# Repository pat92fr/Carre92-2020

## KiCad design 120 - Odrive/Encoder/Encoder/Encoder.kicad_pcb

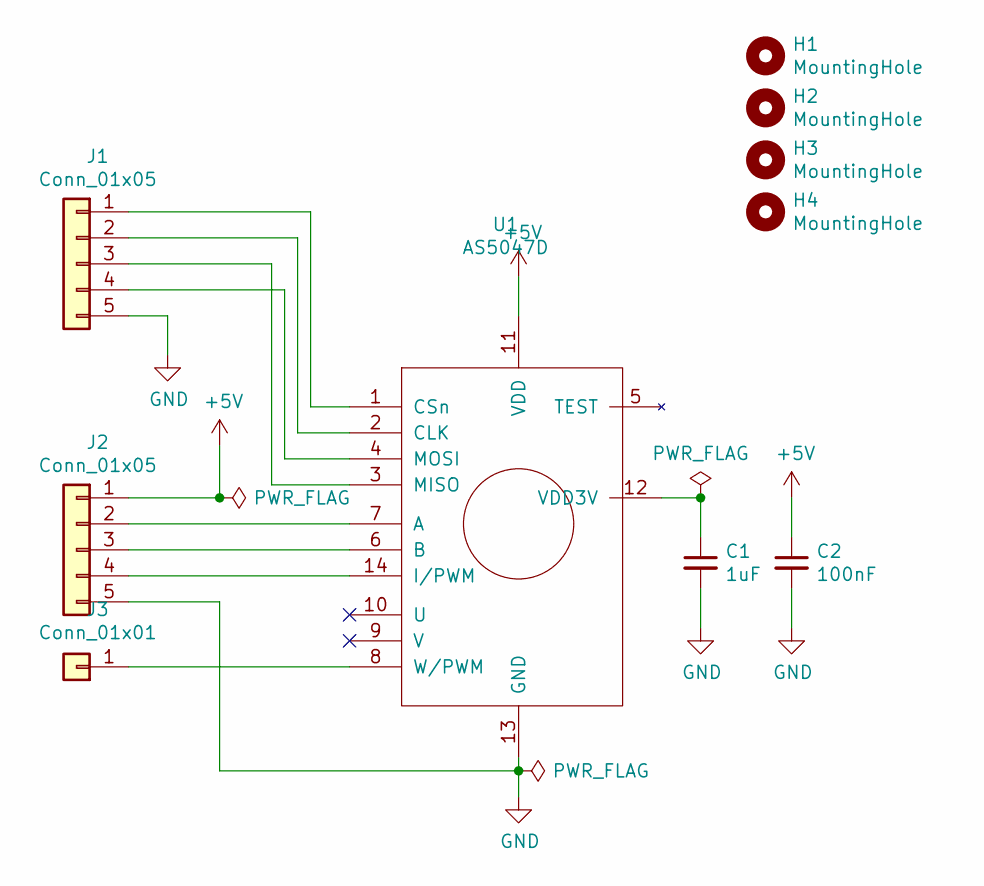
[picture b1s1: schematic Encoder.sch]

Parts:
C1: 1uF; C_0603_HandSoldering
C2: 100nF; C_0603_HandSoldering
H1, H2, H3, H4: MountingHole; MountingHole_4.3mm_M4
J1, J2: Conn_01x05; Pin_Header_Straight_1x05_Pitch2.54mm
J3: Conn_01x01; Pin_Header_Straight_1x01_Pitch2.54mm
U1: AS5047D; TSSOP-14-1EP_4.4x5mm_Pitch0.65mm

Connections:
+5V: C2.1, J2.1, U1.11 (VDD)
GND: C1.2, C2.2, J1.5, J2.5, U1.13 (GND)
unnamed: C1.1, U1.12 (VDD3V)
unnamed: J1.1, U1.1 (CSn)
unnamed: J1.2, U1.2 (CLK)
unnamed: J1.3, U1.3 (MISO)
unnamed: J1.4, U1.4 (MOSI)
unnamed: J2.2, U1.7 (A)
unnamed: J2.3, U1.6 (B)
unnamed: J2.4, U1.14 (I/PWM)
unnamed: J3.1, U1.8 (W/PWM)

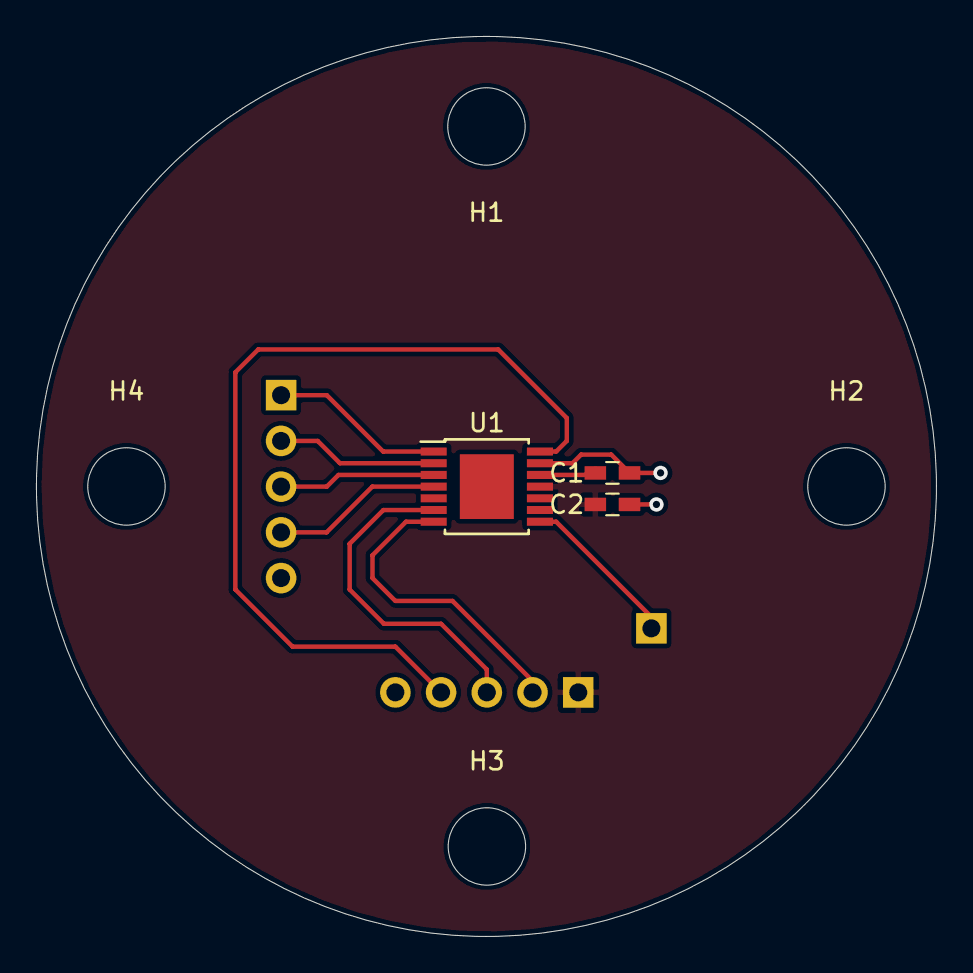
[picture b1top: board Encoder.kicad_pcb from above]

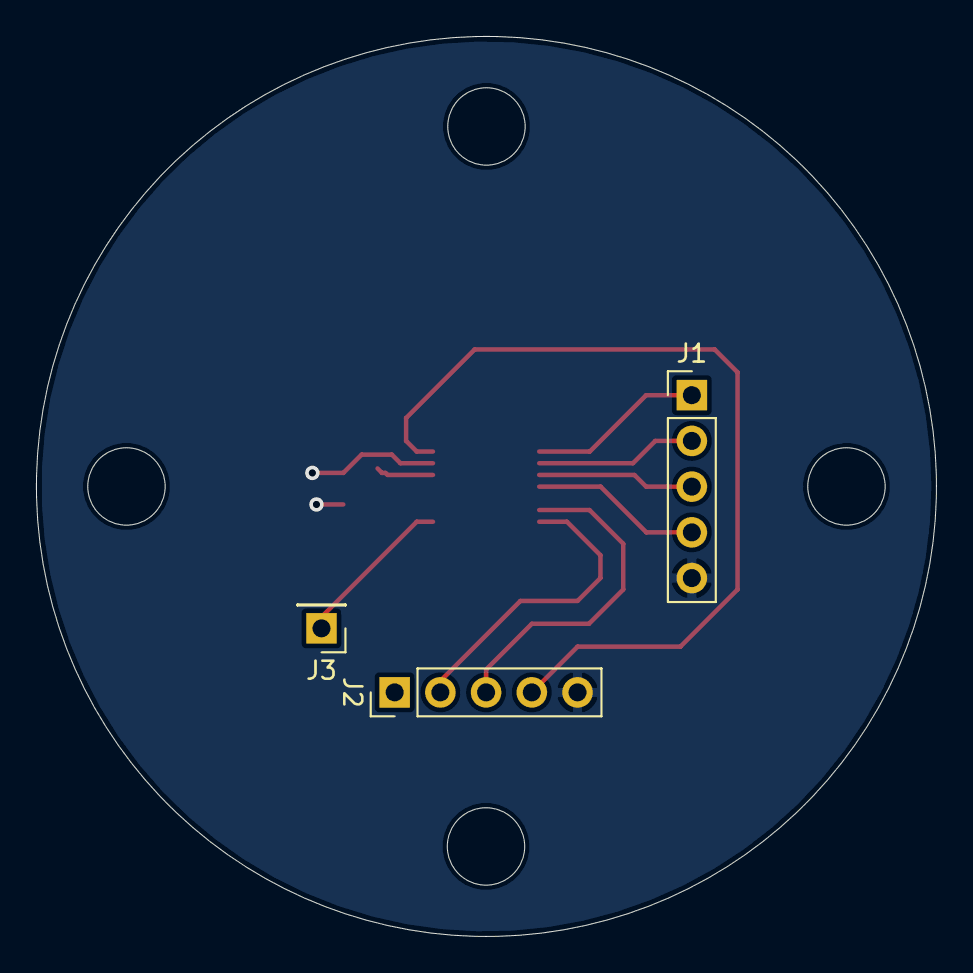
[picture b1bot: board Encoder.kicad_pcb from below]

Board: 2 copper layers, 50.0 x 50.0 mm, 10 parts (3 on the bottom side), 11 nets.

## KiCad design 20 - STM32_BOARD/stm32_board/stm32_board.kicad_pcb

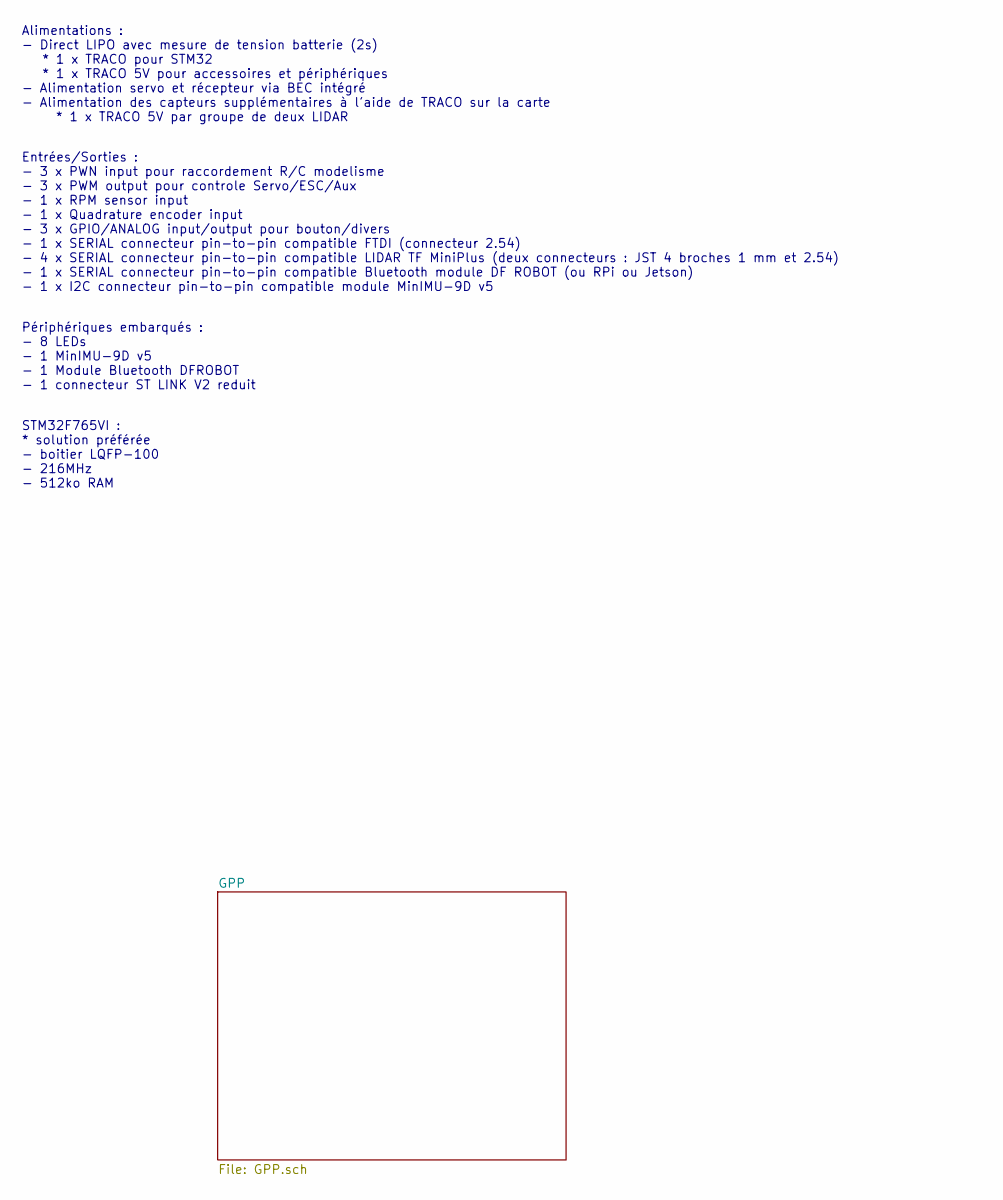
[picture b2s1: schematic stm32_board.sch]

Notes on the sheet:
Alimentations : - Direct LIPO avec mesure de tension batterie (2s) * 1 x TRACO pour STM32 * 1 x TRACO 5V pour accessoires et périphériques - Alimentation servo et récepteur via BEC intégré - Alimentation des capteurs supplémentaires à l'aide de TRACO sur la carte * 1 x TRACO 5V par groupe de deux L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
Entrées/Sorties : - 3 x PWN input pour raccordement R/C modelisme - 3 x PWM output pour controle Servo/ESC/Aux - 1 x RPM sensor input - 1 x Quadrature encoder input - 3 x GPIO/ANALOG input/output pour bouton/divers - 1 x SERIAL connecteur pin-to-pin compatible FTDI (connecteur 2.54) - 4 x SERIAL co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
Périphériques embarqués : - 8 LEDs - 1 MinIMU-9D v5 - 1 Module Bluetooth DFROBOT - 1 connecteur ST LINK V2 reduit
STM32F765VI : * solution préférée - boitier LQFP-100 - 216MHz - 512ko RAM

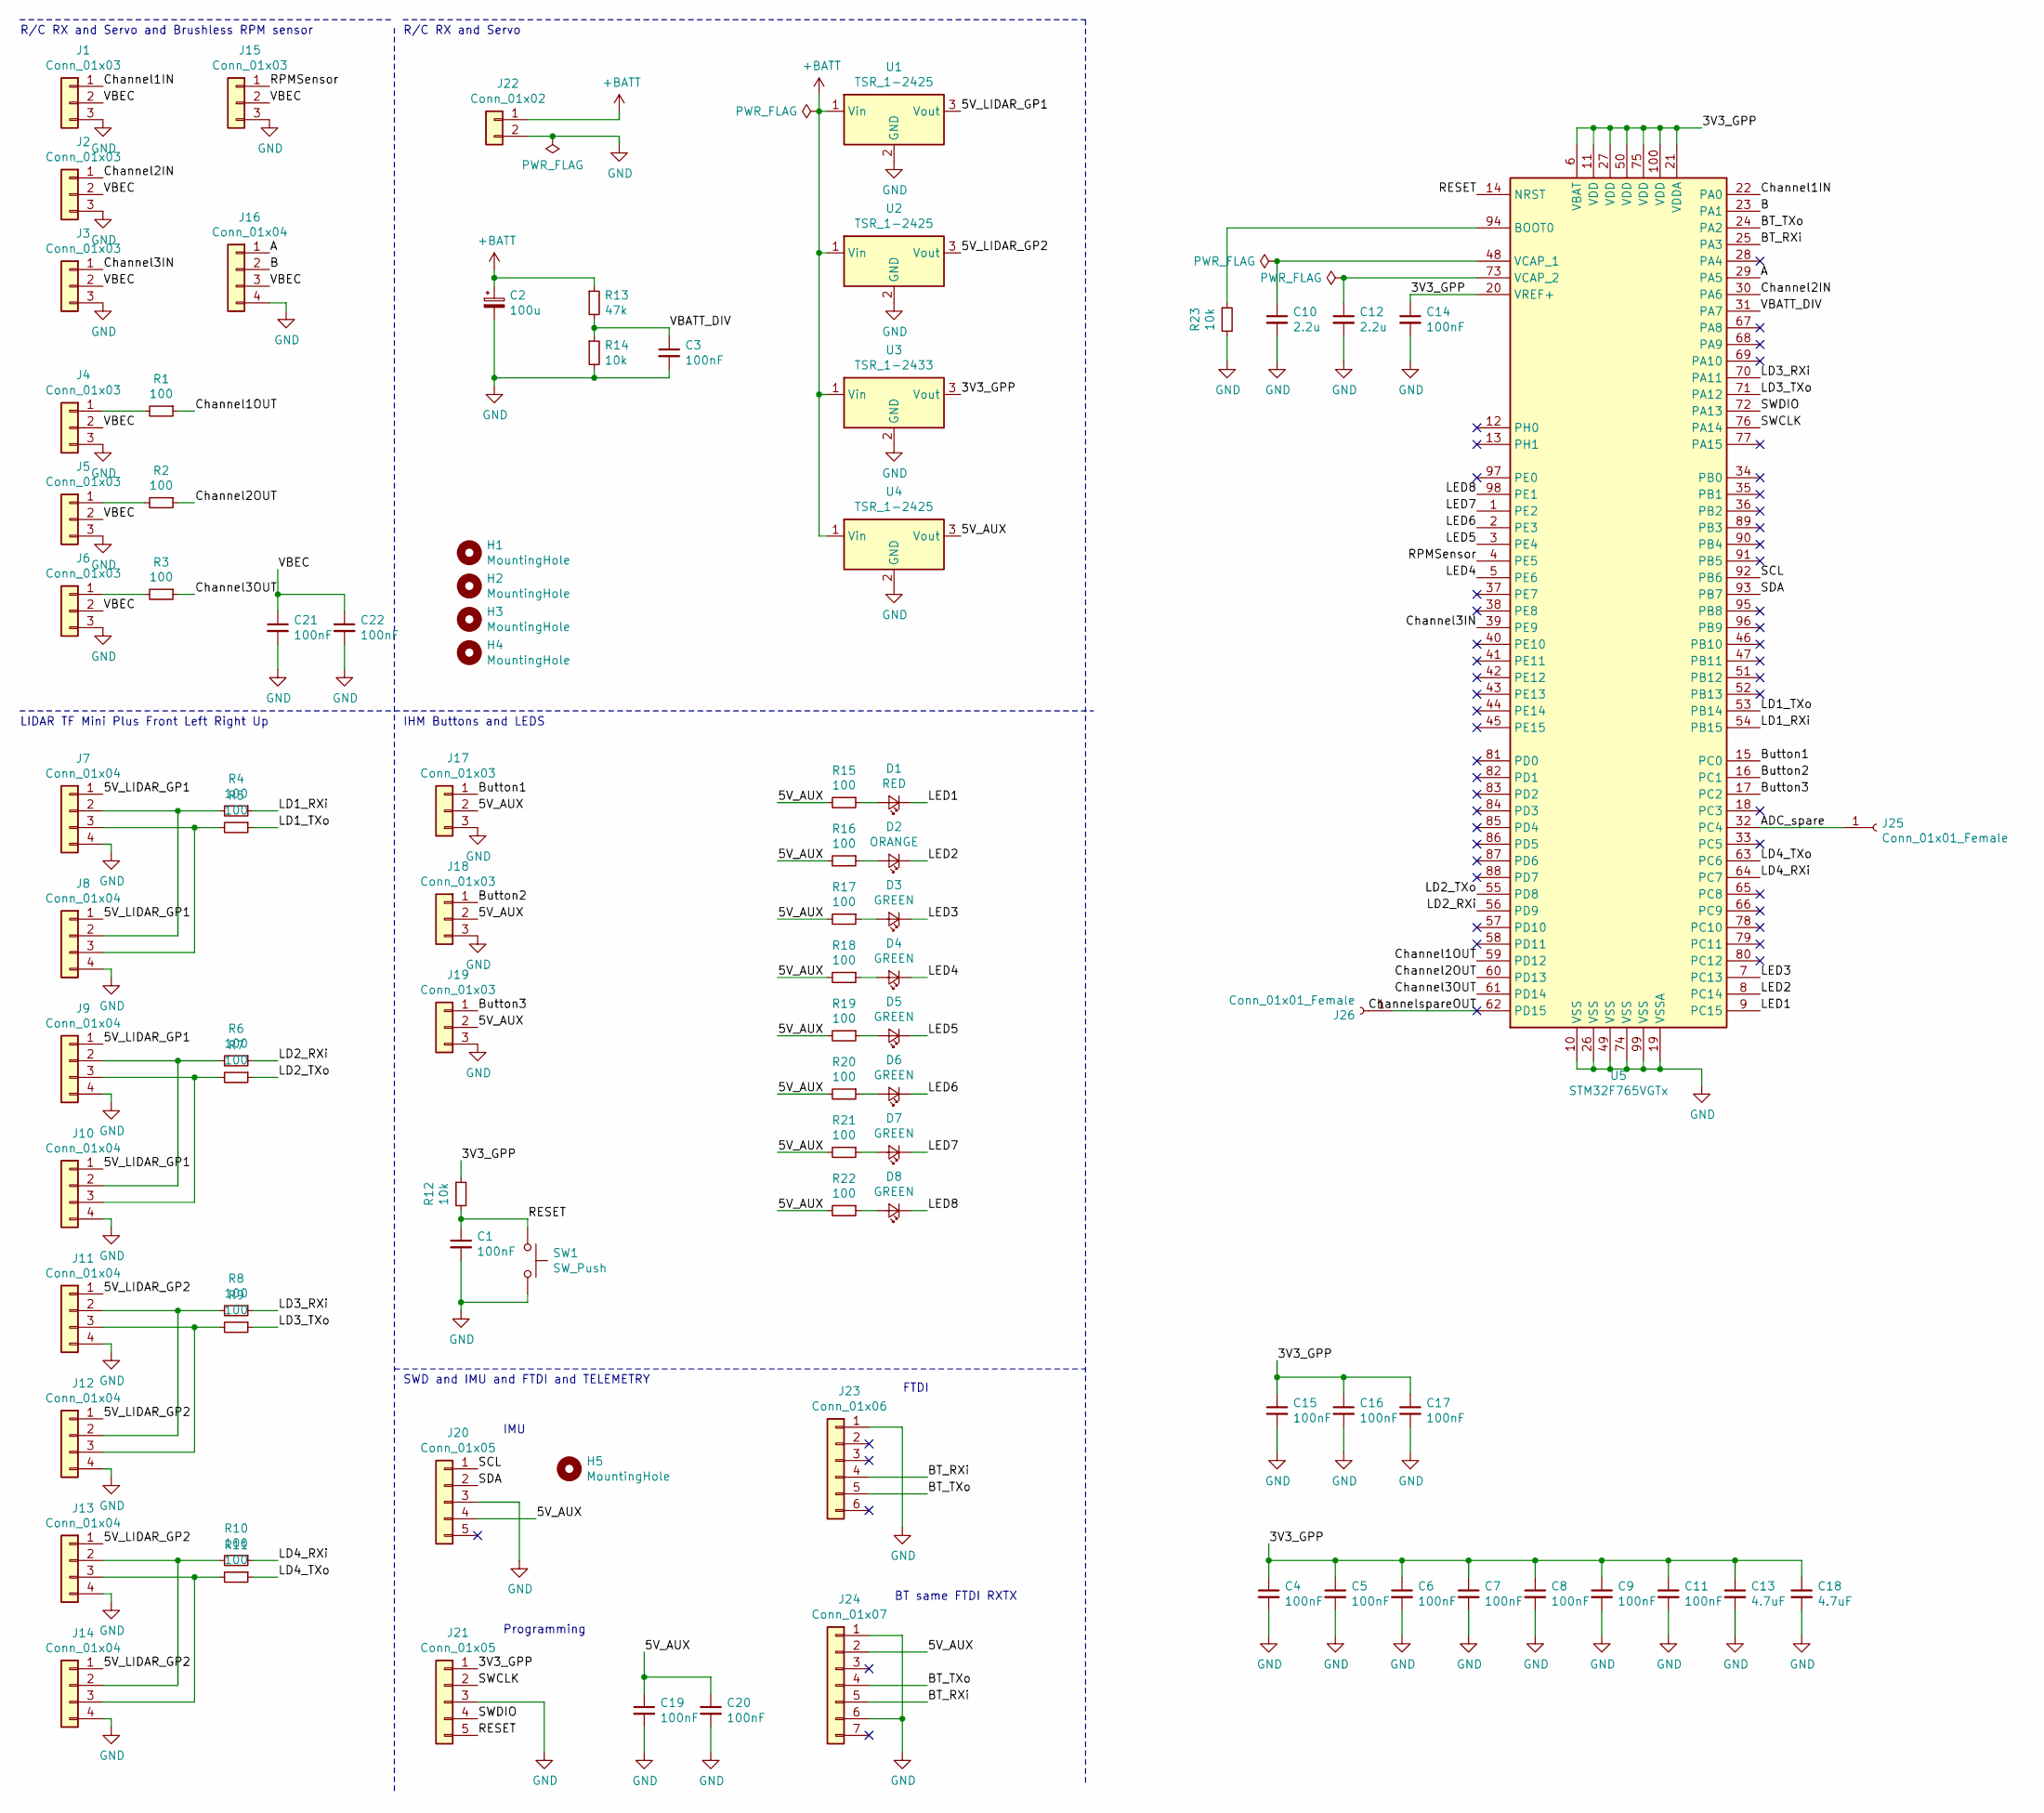
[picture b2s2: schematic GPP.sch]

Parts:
C1, C3, C4, C5, C6, C7, C8, C9, C11: 100nF; C_0603_1608Metric_Pad1.05x0.95mm_HandSolder
C2: 100u; CP_Elec_8x6.9
C10, C12: 2.2u; C_0603_1608Metric_Pad1.05x0.95mm_HandSolder
C13: 4.7uF; C_0603_1608Metric_Pad1.05x0.95mm_HandSolder
C14, C15, C16, C17, C19, C20, C21, C22: 100nF; C_0603_HandSoldering
C18: 4.7uF; C_0603_HandSoldering
D1: RED; LED_0805_2012Metric_Pad1.15x1.40mm_HandSolder
D2: ORANGE; LED_0805_2012Metric_Pad1.15x1.40mm_HandSolder
D3, D4, D5, D6, D7, D8: GREEN; LED_0805_2012Metric_Pad1.15x1.40mm_HandSolder
H1, H2, H3, H4, H5: MountingHole; MountingHole_3.2mm_M3
J1, J2, J3, J4, J5, J6, J15, J17, J18, J19: Conn_01x03; PinHeader_1x03_P2.54mm_Vertical
J7, J9, J11, J13: Conn_01x04; JST_SH_BM04B-SRSS-TB_1x04-1MP_P1.00mm_Vertical
J8, J10, J12, J14, J16: Conn_01x04; PinHeader_1x04_P2.54mm_Vertical
J20, J21: Conn_01x05; PinHeader_1x05_P2.54mm_Vertical
J22: Conn_01x02; PinHeader_1x02_P2.54mm_Vertical
J23: Conn_01x06; PinHeader_1x06_P2.54mm_Vertical
J24: Conn_01x07; PinHeader_1x07_P2.54mm_Vertical
J25, J26: Conn_01x01_Female; Pin_Header_Straight_1x01_Pitch2.54mm
R1, R2, R3, R4, R5, R6, R7, R8, R9, R10, R11, R15, R16, R17, R18, R19, R20, R21, R22: 100; R_0603_1608Metric_Pad1.05x0.95mm_HandSolder
R12, R14, R23: 10k; R_0603_1608Metric_Pad1.05x0.95mm_HandSolder
R13: 47k; R_0603_1608Metric_Pad1.05x0.95mm_HandSolder
SW1: SW_Push; SW_PUSH_6mm
U1, U2, U4: TSR_1-2425; Converter_DCDC_TRACO_TSR-1_THT
U3: TSR_1-2433; Converter_DCDC_TRACO_TSR-1_THT
U5: STM32F765VGTx; LQFP-100_14x14mm_P0.5mm

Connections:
+BATT: C2.1, J22.1, R13.1, U1.1 (Vin), U2.1 (Vin), U3.1 (Vin), U4.1 (Vin)
/GPP/3V3_GPP: C4.1, C5.1, C6.1, C7.1, C8.1, C9.1, C11.1, C13.1, C14.1, C15.1, C16.1, C17.1, C18.1, J21.1, R12.1, U3.3 (Vout), U5.6 (VBAT), U5.11 (VDD), U5.20 (VREF+), U5.21 (VDDA), U5.27 (VDD), U5.50 (VDD), U5.75 (VDD), U5.100 (VDD)
/GPP/5V_AUX: C19.1, C20.1, J17.2, J18.2, J19.2, J20.4, J24.2, R15.2, R16.2, R17.2, R18.2, R19.2, R20.2, R21.2, R22.2, U4.3 (Vout)
/GPP/5V_LIDAR_GP1: J7.1, J8.1, J9.1, J10.1, U1.3 (Vout)
/GPP/5V_LIDAR_GP2: J11.1, J12.1, J13.1, J14.1, U2.3 (Vout)
/GPP/A: J16.1, U5.29 (PA5)
/GPP/ADC_spare: J25.1, U5.32 (PC4)
/GPP/B: J16.2, U5.23 (PA1)
/GPP/BT_RXi: J23.4, J24.5, U5.25 (PA3)
/GPP/BT_TXo: J23.5, J24.4, U5.24 (PA2)
/GPP/Button1: J17.1, U5.15 (PC0)
/GPP/Button2: J18.1, U5.16 (PC1)
/GPP/Button3: J19.1, U5.17 (PC2)
/GPP/Channel1IN: J1.1, U5.22 (PA0)
/GPP/Channel1OUT: R1.1, U5.59 (PD12)
/GPP/Channel2IN: J2.1, U5.30 (PA6)
/GPP/Channel2OUT: R2.1, U5.60 (PD13)
/GPP/Channel3IN: J3.1, U5.39 (PE9)
/GPP/Channel3OUT: R3.1, U5.61 (PD14)
/GPP/ChannelspareOUT: J26.1, U5.62 (PD15)
/GPP/LD1_RXi: R4.1, U5.54 (PB15)
/GPP/LD1_TXo: R5.1, U5.53 (PB14)
/GPP/LD2_RXi: R6.1, U5.56 (PD9)
/GPP/LD2_TXo: R7.1, U5.55 (PD8)
/GPP/LD3_RXi: R8.1, U5.70 (PA11)
/GPP/LD3_TXo: R9.1, U5.71 (PA12)
/GPP/LD4_RXi: R10.1, U5.64 (PC7)
/GPP/LD4_TXo: R11.1, U5.63 (PC6)
/GPP/LED1: D1.1 (K), U5.9 (PC15)
/GPP/LED2: D2.1 (K), U5.8 (PC14)
/GPP/LED3: D3.1 (K), U5.7 (PC13)
/GPP/LED4: D4.1 (K), U5.5 (PE6)
/GPP/LED5: D5.1 (K), U5.3 (PE4)
/GPP/LED6: D6.1 (K), U5.2 (PE3)
/GPP/LED7: D7.1 (K), U5.1 (PE2)
/GPP/LED8: D8.1 (K), U5.98 (PE1)
/GPP/RESET: C1.1, J21.5, R12.2, SW1.1, U5.14 (NRST)
/GPP/RPMSensor: J15.1, U5.4 (PE5)
/GPP/SCL: J20.1, U5.92 (PB6)
/GPP/SDA: J20.2, U5.93 (PB7)
/GPP/SWCLK: J21.2, U5.76 (PA14)
/GPP/SWDIO: J21.4, U5.72 (PA13)
/GPP/VBATT_DIV: C3.1, R13.2, R14.1, U5.31 (PA7)
/GPP/VBEC: C21.1, C22.1, J1.2, J2.2, J3.2, J4.2, J5.2, J6.2, J15.2, J16.3
GND: C1.2, C2.2, C3.2, C4.2, C5.2, C6.2, C7.2, C8.2, C9.2, C10.2, C11.2, C12.2, C13.2, C14.2, C15.2, C16.2, C17.2, C18.2, C19.2, C20.2, C21.2, C22.2, J1.3, J2.3, J3.3, J4.3, J5.3, J6.3, J7.4, J8.4, J9.4, J10.4, J11.4, J12.4, J13.4, J14.4, J15.3, J16.4, J17.3, J18.3, J19.3, J20.3, J21.3, J22.2, J23.1, J24.1, J24.6, R14.2, R23.2, SW1.2, U1.2 (GND), U2.2 (GND), U3.2 (GND), U4.2 (GND), U5.10 (VSS), U5.19 (VSSA), U5.26 (VSS), U5.49 (VSS), U5.74 (VSS), U5.99 (VSS)
unnamed: C10.1, U5.48 (VCAP_1)
unnamed: C12.1, U5.73 (VCAP_2)
unnamed: D1.2 (A), R15.1
unnamed: D2.2 (A), R16.1
unnamed: D3.2 (A), R17.1
unnamed: D4.2 (A), R18.1
unnamed: D5.2 (A), R19.1
unnamed: D6.2 (A), R20.1
unnamed: D7.2 (A), R21.1
unnamed: D8.2 (A), R22.1
unnamed: J4.1, R1.2
unnamed: J5.1, R2.2
unnamed: J6.1, R3.2
unnamed: J7.2, J8.2, R4.2
unnamed: J7.3, J8.3, R5.2
unnamed: J9.2, J10.2, R6.2
unnamed: J9.3, J10.3, R7.2
unnamed: J11.2, J12.2, R8.2
unnamed: J11.3, J12.3, R9.2
unnamed: J13.2, J14.2, R10.2
unnamed: J13.3, J14.3, R11.2
unnamed: R23.1, U5.94 (BOOT0)

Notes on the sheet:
LIDAR TF Mini Plus Front Left Right Up
R/C RX and Servo and Brushless RPM sensor
R/C RX and Servo
IHM Buttons and LEDS
SWD and IMU and FTDI and TELEMETRY
Programming
IMU
BT same FTDI RXTX
FTDI

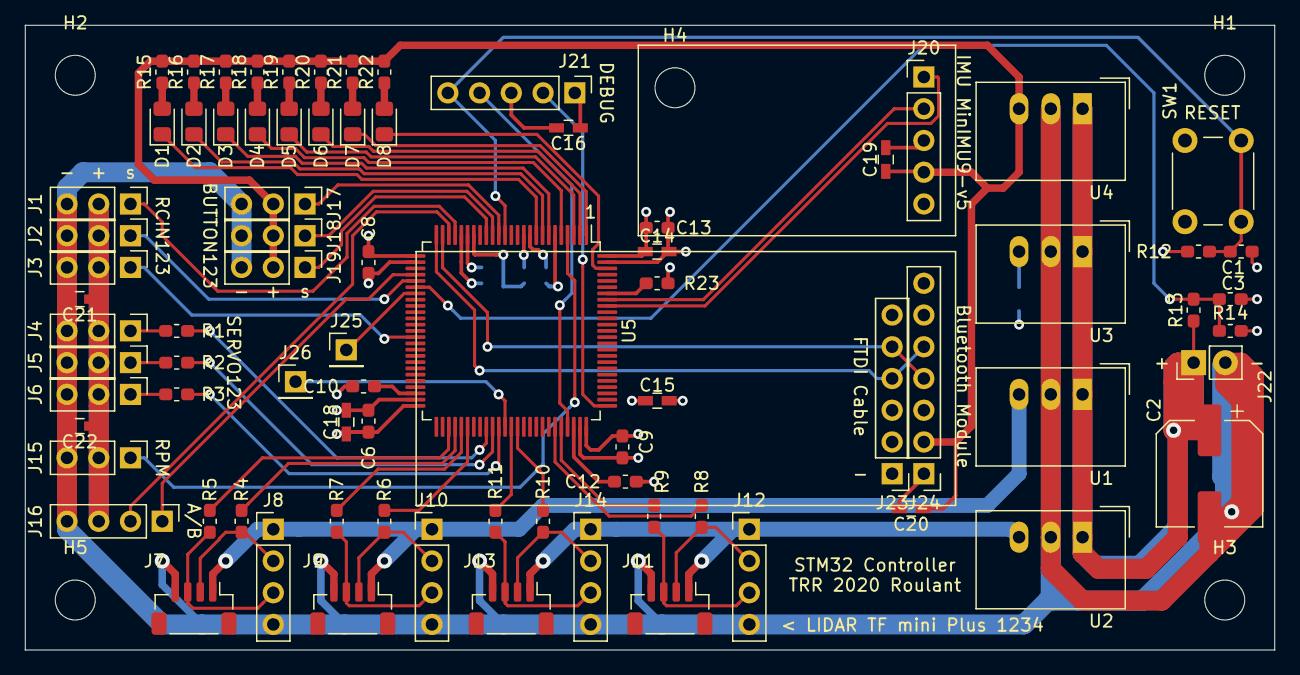
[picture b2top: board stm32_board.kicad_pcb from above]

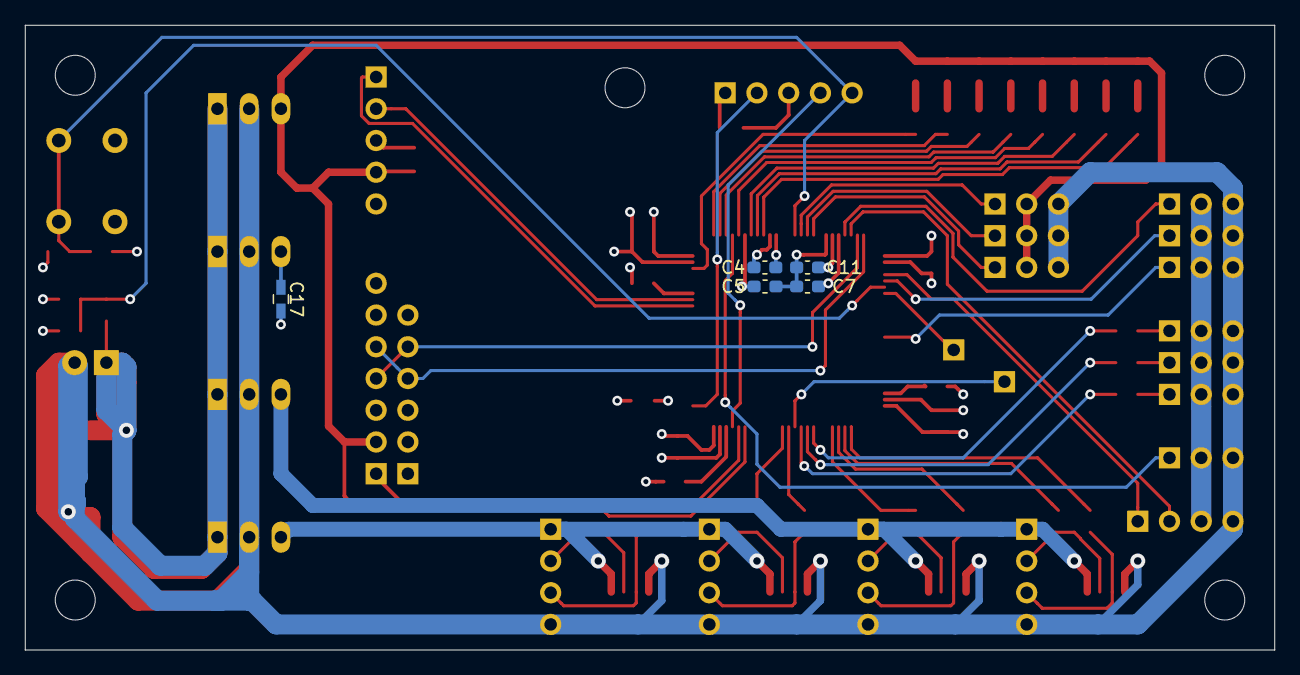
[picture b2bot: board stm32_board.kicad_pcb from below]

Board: 4 copper layers, 100.0 x 50.0 mm, 90 parts (5 on the bottom side), 67 nets.

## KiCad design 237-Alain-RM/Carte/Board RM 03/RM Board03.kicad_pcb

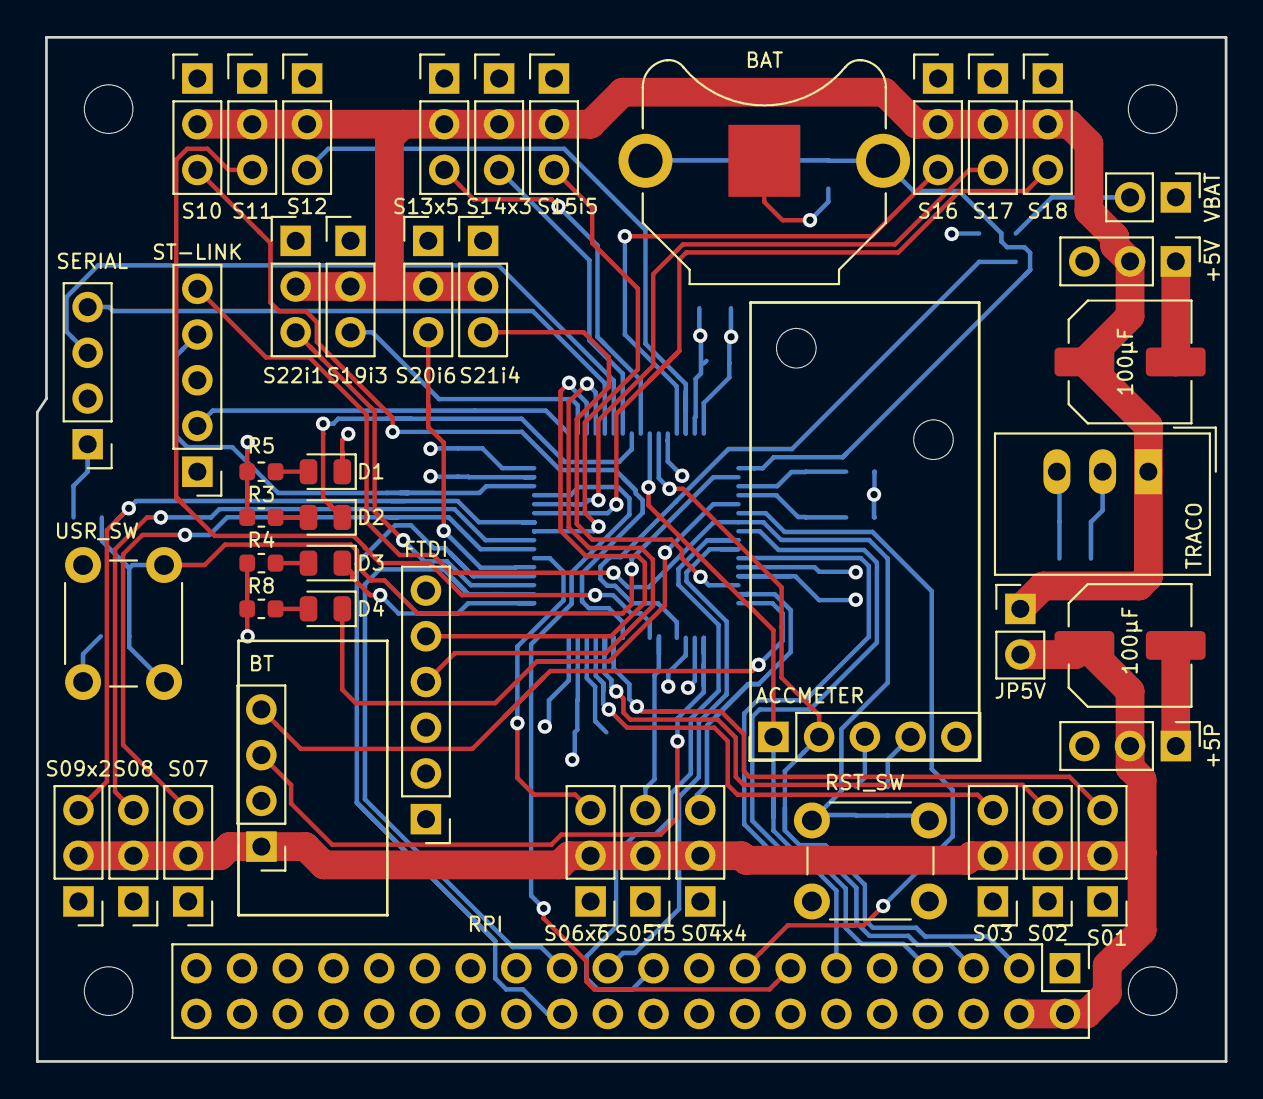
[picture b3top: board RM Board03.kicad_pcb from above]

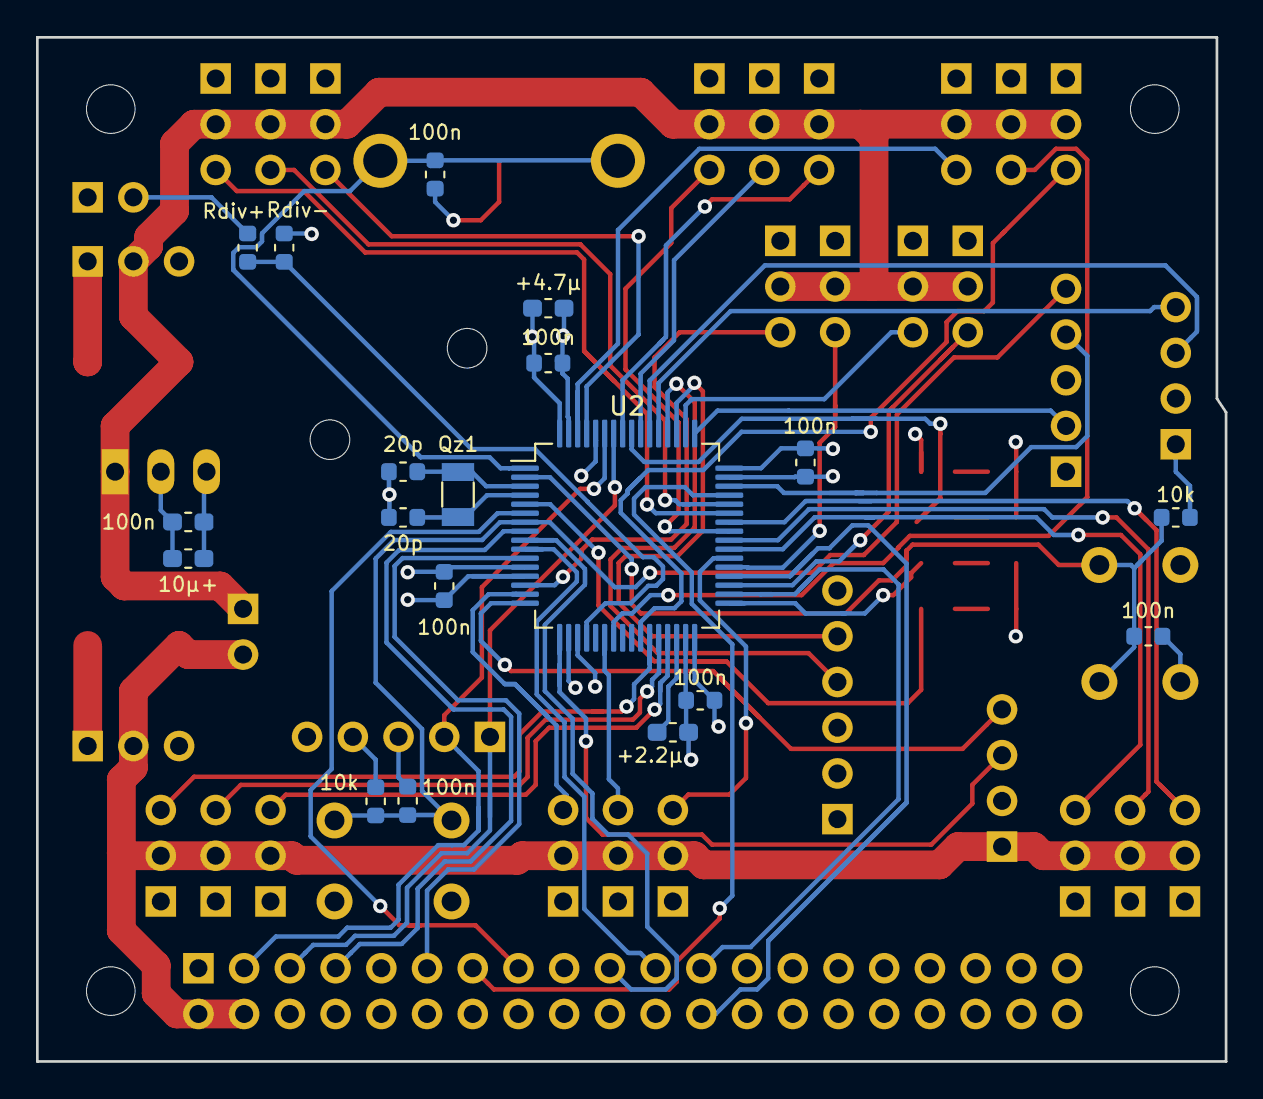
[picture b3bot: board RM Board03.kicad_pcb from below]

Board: 4 copper layers, 66.0 x 56.9 mm, 69 parts (19 on the bottom side), 59 nets.

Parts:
10k, 10k#2: 10K; R_0603_1608Metric
10µ+: 10µF; C_0603_1608Metric_Pad1.05x0.95mm_HandSolder
20p, 20p#2: 20pF; C_0603_1608Metric
100n, 100n#2, 100n#3, 100n#4, 100n#6, 100n#7, 100n#8: 100nF; C_0603_1608Metric
100n#5: 100nF; C_0603_1608Metric_Pad1.05x0.95mm_HandSolder
100µF, 100µF#2: 100nF; C_Elec_6.3x5.8
 : MountingHole_2.7mm_M2.5
 #2: MountingHole_2.7mm_M2.5
 #3: MH3; MountingHole_2.7mm_M2.5
 #4: MH4; MountingHole_2.7mm_M2.5
+2.2µ: 2.2µF; C_0603_1608Metric_Pad1.05x0.95mm_HandSolder
+4.7µ: 4.7µF; C_0603_1608Metric_Pad1.05x0.95mm_HandSolder
+5P: BEC_2; PinHeader_1x03_P2.54mm_Vertical
+5V: BEC_1; PinHeader_1x03_P2.54mm_Vertical
ACCMETER: ACCMETER; Altimu
BAT: Battery; BatteryHolder_Keystone_3001_1x12mm
BT: SER_BT; SH_BT_Board_v1.3
D1, D2, D3, D4: LED; LED_0805_2012Metric
FTDI: FTDI; PinHeader_1x06_P2.54mm_Vertical
JP5V: JP_BEC; PinHeader_1x02_P2.54mm_Vertical
Qz1: 32kHz; Crystal_SMD_3215-2Pin_3.2x1.5mm
R3, R4, R5, R8: 60; R_0603_1608Metric
RPI: PinHeader_2x20_P2.54mm_Vertical
RST_SW: SW_RST; SW_PUSH_6mm_H4.3mm
Rdiv+: 47K; R_0603_1608Metric
Rdiv-: 22K; R_0603_1608Metric
S01: S01; PinHeader_1x03_P2.54mm_Vertical
S02: S02; PinHeader_1x03_P2.54mm_Vertical
S03: S03; PinHeader_1x03_P2.54mm_Vertical
S04x4: S04x4; PinHeader_1x03_P2.54mm_Vertical
S05i5: S05i5; PinHeader_1x03_P2.54mm_Vertical
S06x6: S06x6; PinHeader_1x03_P2.54mm_Vertical
S07, S08, S09x2, S10, S11: PinHeader_1x03_P2.54mm_Vertical
S12: S12; PinHeader_1x03_P2.54mm_Vertical
S13x5: S13x5; PinHeader_1x03_P2.54mm_Vertical
S14x3: S14x3; PinHeader_1x03_P2.54mm_Vertical
S15i5: S15i2; PinHeader_1x03_P2.54mm_Vertical
S16: S16; PinHeader_1x03_P2.54mm_Vertical
S17: S17; PinHeader_1x03_P2.54mm_Vertical
S18: S18; PinHeader_1x03_P2.54mm_Vertical
S19i3: S19i3; PinHeader_1x03_P2.54mm_Vertical
S20i6: S20i6; PinHeader_1x03_P2.54mm_Vertical
S21i4: S21i4; PinHeader_1x03_P2.54mm_Vertical
S22i1: S22i1; PinHeader_1x03_P2.54mm_Vertical
SERIAL: PinHeader_1x04_P2.54mm_Vertical
ST-LINK: PinHeader_1x05_P2.54mm_Vertical
TRACO: TSR_1-2433; Converter_DCDC_TRACO_TSR-1_THT
U2: STM32F446RETx; LQFP-64_10x10mm_P0.5mm
USR_SW: SW_PUSH_6mm_H4.3mm
VBAT: BATT; PinHeader_1x02_P2.54mm_Vertical

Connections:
+3V3: 10k.1, 10k#2.1, 10µ+.1, 100n#3.1, 100n#4.1, 100n#5.1, 100n#6.1, 100n#7.1, +4.7µ.1, ACCMETER.4, R3.1, R4.1, R5.1, R8.1, SERIAL.1, ST-LINK.1, TRACO.3, U2.13, U2.19, U2.32, U2.48, U2.64
+5P: 100µF.1, +5V.2, JP5V.1, S10.2, S11.2, S12.2, S13x5.2, S14x3.2, S15i5.2, S16.2, S17.2, S18.2, S19i3.2, S20i6.2, S21i4.2, S22i1.2, TRACO.1
+5V: 100µF#2.1, +5P.2, BT.1, JP5V.2, RPI.2, RPI.4, S01.2, S02.2, S03.2, S04x4.2, S05i5.2, S06x6.2, S07.2, S08.2, S09x2.2
ADC_IN: Rdiv+.2, Rdiv-.1, U2.20
CE0: RPI.24, U2.36
FTDI_RX: FTDI.4, U2.52
FTDI_TX: FTDI.5, U2.51
GND: 10µ+.2, 20p.2, 20p#2.2, 100n.2, 100n#2.2, 100n#3.2, 100n#4.2, 100n#5.2, 100n#6.2, 100n#7.2, 100n#8.2, 100µF.2, 100µF#2.2, +2.2µ.2, +4.7µ.2, +5P.1, +5V.1, ACCMETER.3, BAT.2, BT.2, D1.1, FTDI.1, RPI.6, RPI.9, RPI.14, RPI.20, RPI.25, RPI.30, RPI.34, RPI.39, RST_SW.1, Rdiv-.2, S01.1, S02.1, S03.1, S04x4.1, S05i5.1, S06x6.1, S07.1, S08.1, S09x2.1, S10.1, S11.1, S12.1, S13x5.1, S14x3.1, S15i5.1, S16.1, S17.1, S18.1, S19i3.1, S20i6.1, S21i4.1, S22i1.1, SERIAL.2, ST-LINK.3, TRACO.2, U2.12, U2.18, U2.31, U2.47, U2.60, U2.63, USR_SW.1, VBAT.1
I2C_SCL: ACCMETER.1, RPI.5, U2.58
I2C_SDA: ACCMETER.2, RPI.3, U2.59
IO_IN_1: RPI.13, U2.45
IO_IN_2: RPI.15, U2.6
IO_OUT_1: RPI.7, U2.8
IO_OUT_2: RPI.11, U2.11
LED1: D2.1, U2.56
LED2: D3.1, U2.33
LED3: D4.1, U2.5
unnamed: D2.2, R3.2
unnamed: D3.2, R4.2
unnamed: D4.2, R8.2
unnamed: D1.2, R5.2
OSC_1: 20p.1, Qz1.1, U2.3
OSC_2: 20p#2.1, Qz1.2, U2.4
Pile: 100n#8.1, BAT.1, U2.1
RST: 10k#2.2, 100n#2.1, RST_SW.2, ST-LINK.5, U2.7
S01: S01.3, U2.27
S02: S02.3, U2.28
S03: S03.3, U2.29
S04: S04x4.3, U2.15
S05: S05i5.3, U2.22
S06: S06x6.3, U2.38
S07: S07.3, U2.39
S08: S08.3, U2.40
S09: S09x2.3, U2.42
S10: S10.3, U2.26
S11: S11.3, U2.23
S12: S12.3, U2.62
S13: S13x5.3, U2.57
S14: S14x3.3, U2.55
S15: S15i5.3, U2.41
S16: S16.3, U2.61
S17: S17.3, U2.44
S18: S18.3, U2.43
S19: S19i3.3, U2.50
S20: S20i6.3, U2.37
S21: S21i4.3, U2.14
S22: S22i1.3, U2.35
SPI2_MISO: RPI.21, U2.10
SPI2_MOSI: RPI.19, U2.9
SPI2_SCK: RPI.23, U2.34
SWCLK: ST-LINK.2, U2.49
SWDIO: ST-LINK.4, U2.46
UART2_RX: BT.3, U2.17
UART2_TX: BT.4, U2.16
UART5_RX: RPI.8, SERIAL.3, U2.54
UART5_TX: RPI.10, SERIAL.4, U2.53
USR_BUTT: 10k.2, 100n.1, U2.2, USR_SW.2
VBAT: Rdiv+.1, VBAT.2
VCAP_1: +2.2µ.1, U2.30

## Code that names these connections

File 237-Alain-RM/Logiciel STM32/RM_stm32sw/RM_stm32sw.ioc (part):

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Mcu.Name=STM32F446R(C-E)Tx
Mcu.Package=LQFP64
Mcu.UserName=STM32F446RETx
PA0-WKUP.GPIOParameters=GPIO_Label
PA0-WKUP.GPIO_Label=S21i4
PA0-WKUP.Signal=S_TIM5_CH1
PA1.GPIOParameters=GPIO_Label
PA1.GPIO_Label=S04x4
PA1.Signal=S_TIM5_CH2
PA10.GPIOParameters=GPIO_Label
PA10.GPIO_Label=S18
PA10.Signal=S_TIM1_CH3
PA11.GPIOParameters=GPIO_Label
PA11.GPIO_Label=S17
PA11.Signal=S_TIM1_CH4
PA13.GPIOParameters=GPIO_Label
PA13.GPIO_Label=SWDIO
PA13.Mode=Serial_Wire
PA13.Signal=SYS_JTMS-SWDIO
PA14.GPIOParameters=GPIO_Label
PA14.GPIO_Label=SWCLK
PA14.Mode=Serial_Wire
PA14.Signal=SYS_JTCK-SWCLK
PA15.GPIOParameters=GPIO_Label
PA15.GPIO_Label=S19i3
PA15.Signal=S_TIM2_CH1_ETR
PA2.GPIOParameters=GPIO_Label
PA2.GPIO_Label=UART2_TX
PA2.Mode=Asynchronous
PA2.Signal=USART2_TX
PA3.GPIOParameters=GPIO_Label
PA3.GPIO_Label=UART2_RX
PA3.Mode=Asynchronous
PA3.Signal=USART2_RX
PA4.GPIOParameters=GPIO_Label
PA4.GPIO_Label=ADC_IN
PA4.Signal=ADCx_IN4
PA6.GPIOParameters=GPIO_Label
PA6.GPIO_Label=S05i5
PA6.Signal=S_TIM3_CH1
PA7.GPIOParameters=GPIO_Label
PA7.GPIO_Label=S11
PA7.Signal=S_TIM14_CH1
PA8.GPIOParameters=GPIO_Label
PA8.GPIO_Label=S15i2
PA8.Signal=S_TIM1_CH1
PA9.GPIOParameters=GPIO_Label
PA9.GPIO_Label=S09x2
PA9.Signal=S_TIM1_CH2
PB0.GPIOParameters=GPIO_Label
PB0.GPIO_Label=S10
PB0.Signal=S_TIM3_CH3
PB1.GPIOParameters=GPIO_Label
PB1.GPIO_Label=S01
PB1.Signal=S_TIM3_CH4
PB10.GPIOParameters=GPIO_Label
PB10.GPIO_Label=S03
PB10.Signal=S_TIM2_CH3
PB12.GPIOParameters=GPIO_Label
PB12.GPIO_Label=LED3
PB12.Signal=GPIO_Output
PB13.GPIOParameters=GPIO_Label
PB13.GPIO_Label=SPI2_SCK
PB13.Mode=Full_Duplex_Master
PB13.Signal=SPI2_SCK
PB14.GPIOParameters=GPIO_Label
PB14.GPIO_Label=S22i1
PB14.Signal=S_TIM12_CH1
PB2.GPIOParameters=GPIO_Label
PB2.GPIO_Label=S02
PB2.Signal=S_TIM2_CH4
PB3.GPIOParameters=GPIO_Label
PB3.GPIO_Label=S14x3
PB3.Signal=S_TIM2_CH2
PB4.GPIOParameters=GPIO_Label
PB4.GPIO_Label=LED2
PB4.Signal=GPIO_Output
PB5.GPIOParameters=GPIO_Label
PB5.GPIO_Label=S13x5
PB5.Signal=S_TIM3_CH2
PB6.GPIOParameters=GPIO_Label
PB6.GPIO_Label=I2C_SCL
PB6.Mode=I2C
PB6.Signal=I2C1_SCL
PB7.GPIOParameters=GPIO_Label
PB7.GPIO_Label=I2C_SDA
PB7.Mode=I2C
PB7.Signal=I2C1_SDA
PB8.GPIOParameters=GPIO_Label
PB8.GPIO_Label=S16
PB8.Signal=S_TIM10_CH1
PB9.GPIOParameters=GPIO_Label
PB9.GPIO_Label=S12
PB9.Signal=S_TIM11_CH1
PC0.GPIOParameters=GPIO_Label
PC0.GPIO_Label=IO_OUT_1
PC0.Signal=GPIO_Output
PC1.GPIOParameters=GPIO_Label
PC1.GPIO_Label=SPI2_MOSI
PC1.Mode=Full_Duplex_Master
PC1.Signal=SPI2_MOSI
PC10.GPIOParameters=GPIO_Label
PC10.GPIO_Label=FTDI_TX
PC10.Mode=Asynchronous
PC10.Signal=UART4_TX
PC11.GPIOParameters=GPIO_Label
PC11.GPIO_Label=FTDI_RX
PC11.Mode=Asynchronous
PC11.Signal=UART4_RX
PC12.GPIOParameters=GPIO_Label
PC12.GPIO_Label=UART5_TX
PC12.Mode=Asynchronous
PC12.Signal=UART5_TX
PC13.GPIOParameters=GPIO_Label
PC13.GPIO_Label=USR_BUTT
PC13.Signal=GPIO_Input
PC14-OSC32_IN.GPIOParameters=GPIO_Label
PC14-OSC32_IN.GPIO_Label=OSC_IN
PC14-OSC32_IN.Signal=RCC_OSC32_IN
PC15-OSC32_OUT.GPIOParameters=GPIO_Label
PC15-OSC32_OUT.GPIO_Label=OSC_OUT
PC15-OSC32_OUT.Signal=RCC_OSC32_OUT
PC2.GPIOParameters=GPIO_Label
PC2.GPIO_Label=SPI2_MISO
PC2.Mode=Full_Duplex_Master
PC2.Signal=SPI2_MISO
PC3.GPIOParameters=GPIO_Label
PC3.GPIO_Label=IO_OUT_2
PC3.Signal=GPIO_Output
PC6.GPIOParameters=GPIO_Label
PC6.GPIO_Label=S20i6
PC6.Signal=S_TIM8_CH1
PC7.GPIOParameters=GPIO_Label
PC7.GPIO_Label=S06x6
PC7.Signal=S_TIM8_CH2
PC8.GPIOParameters=GPIO_Label
PC8.GPIO_Label=S07
PC8.Signal=S_TIM8_CH3
PC9.GPIOParameters=GPIO_Label
PC9.GPIO_Label=S08
PC9.Signal=S_TIM8_CH4
PD2.GPIOParameters=GPIO_Label
PD2.GPIO_Label=UART5_RX
PD2.Mode=Asynchronous
PD2.Signal=UART5_RX
PH0-OSC_IN.GPIOParameters=GPIO_Label
PH0-OSC_IN.GPIO_Label=LED4
PH0-OSC_IN.Signal=GPIO_Output
PH1-OSC_OUT.GPIOParameters=GPIO_Label
PH1-OSC_OUT.GPIO_Label=IO_IN_2
PH1-OSC_OUT.Signal=GPIO_Input
RCC.SYSCLKFreq_VALUE=180000000
RCC.SYSCLKSource=RCC_SYSCLKSOURCE_PLLCLK
board=custom

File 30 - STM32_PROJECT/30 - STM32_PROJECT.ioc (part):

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Mcu.Name=STM32F765V(G-I)Tx
Mcu.Package=LQFP100
Mcu.UserName=STM32F765VITx
PA0/WKUP.Signal=S_TIM5_CH1
PA1.Signal=S_TIM2_CH2
PA11.Mode=Asynchronous
PA11.Signal=UART4_RX
PA12.Mode=Asynchronous
PA12.Signal=UART4_TX
PA13.Mode=Serial_Wire
PA13.Signal=SYS_JTMS-SWDIO
PA14.Mode=Serial_Wire
PA14.Signal=SYS_JTCK-SWCLK
PA2.Mode=Asynchronous
PA2.Signal=USART2_TX
PA3.Mode=Asynchronous
PA3.Signal=USART2_RX
PA5.Signal=S_TIM2_CH1_ETR
PA6.Signal=S_TIM3_CH1
PA7.Signal=ADCx_IN7
PB10.Mode=Asynchronous
PB10.Signal=USART3_TX
PB11.Mode=Asynchronous
PB11.Signal=USART3_RX
PB14.Mode=Asynchronous
PB14.Signal=USART1_TX
PB15.Mode=Asynchronous
PB15.Signal=USART1_RX
PB6.Mode=I2C
PB6.Signal=I2C1_SCL
PB7.Mode=I2C
PB7.Signal=I2C1_SDA
PC4.Signal=ADCx_IN14
PC6.Mode=Asynchronous
PC6.Signal=USART6_TX
PC7.Mode=Asynchronous
PC7.Signal=USART6_RX
PD12.Signal=S_TIM4_CH1
PD13.Signal=S_TIM4_CH2
PD14.Signal=S_TIM4_CH3
PD15.Signal=S_TIM4_CH4
PE5.Signal=S_TIM9_CH1
PE9.Signal=S_TIM1_CH1
RCC.HSE_VALUE=25000000
board=custom

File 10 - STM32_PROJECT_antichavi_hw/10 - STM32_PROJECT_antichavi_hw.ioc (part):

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Mcu.Name=STM32F415RGTx
Mcu.Package=LQFP64
Mcu.UserName=STM32F415RGTx
PA1.Mode=Asynchronous
PA1.Signal=UART4_RX
PA10.Signal=S_TIM1_CH3
PA11.Signal=S_TIM1_CH4
PA13.Mode=Serial_Wire
PA13.Signal=SYS_JTMS-SWDIO
PA14.Mode=Serial_Wire
PA14.Signal=SYS_JTCK-SWCLK
PA2.Mode=Asynchronous
PA2.Signal=USART2_TX
PA3.Mode=Asynchronous
PA3.Signal=USART2_RX
PA6.GPIOParameters=GPIO_Label
PA6.GPIO_Label=RX2
PA6.Signal=S_TIM3_CH1
PA8.Signal=S_TIM1_CH1
PA9.Signal=S_TIM1_CH2
PB10.Mode=Asynchronous
PB10.Signal=USART3_TX
PB11.Mode=Asynchronous
PB11.Signal=USART3_RX
PB14.GPIOParameters=GPIO_Label
PB14.GPIO_Label=RX4
PB14.Signal=S_TIM12_CH1
PB3.GPIOParameters=GPIO_Label,GPIO_ModeDefaultOutputPP
PB3.GPIO_Label=LED2
PB3.GPIO_ModeDefaultOutputPP=GPIO_MODE_OUTPUT_OD
PB3.Signal=GPIO_Output
PB4.GPIOParameters=GPIO_Label,GPIO_ModeDefaultOutputPP
PB4.GPIO_Label=LED0
PB4.GPIO_ModeDefaultOutputPP=GPIO_MODE_OUTPUT_OD
PB4.Signal=GPIO_Output
PB5.GPIOParameters=GPIO_Label,GPIO_ModeDefaultOutputPP
PB5.GPIO_Label=LED1
PB5.GPIO_ModeDefaultOutputPP=GPIO_MODE_OUTPUT_OD
PB5.Signal=GPIO_Output
PB6.GPIOParameters=GPIO_PuPd,GPIO_Label
PB6.GPIO_Label=RX3
PB6.GPIO_PuPd=GPIO_PULLUP
PB6.Signal=S_TIM4_CH1
PB7.Mode=I2C
PB7.Signal=I2C1_SDA
PB8.Mode=I2C
PB8.Signal=I2C1_SCL
PC10.Mode=Asynchronous
PC10.Signal=UART4_TX
PC12.Mode=Asynchronous
PC12.Signal=UART5_TX
PC15-OSC32_OUT.GPIOParameters=GPIO_Label,GPIO_ModeDefaultOutputPP
PC15-OSC32_OUT.GPIO_Label=LED5
PC15-OSC32_OUT.GPIO_ModeDefaultOutputPP=GPIO_MODE_OUTPUT_OD
PC15-OSC32_OUT.Signal=GPIO_Output
PC4.GPIOParameters=GPIO_PuPd,GPIO_Label,GPIO_ModeDefaultEXTI
PC4.GPIO_Label=START_BUTTON
PC4.GPIO_ModeDefaultEXTI=GPIO_MODE_IT_RISING
PC4.GPIO_PuPd=GPIO_PULLUP
PC4.Signal=GPXTI4
PC6.Signal=S_TIM8_CH1
PC7.Signal=S_TIM8_CH2
PC8.Signal=S_TIM8_CH3
PC9.Signal=S_TIM8_CH4
PD2.Mode=Asynchronous
PD2.Signal=UART5_RX
PH0-OSC_IN.GPIOParameters=GPIO_Label,GPIO_ModeDefaultOutputPP
PH0-OSC_IN.GPIO_Label=LED4
PH0-OSC_IN.GPIO_ModeDefaultOutputPP=GPIO_MODE_OUTPUT_OD
PH0-OSC_IN.Signal=GPIO_Output
PH1-OSC_OUT.GPIOParameters=GPIO_Label,GPIO_ModeDefaultOutputPP
PH1-OSC_OUT.GPIO_Label=LED3
PH1-OSC_OUT.GPIO_ModeDefaultOutputPP=GPIO_MODE_OUTPUT_OD
PH1-OSC_OUT.Signal=GPIO_Output
RCC.HSE_VALUE=25000000
RCC.SYSCLKFreq_VALUE=168000000
RCC.SYSCLKSource=RCC_SYSCLKSOURCE_PLLCLK
board=custom

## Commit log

2019-10-08 RETEX
2019-10-12 stm32
2019-10-13 simulator
2019-10-14 circuit
2019-10-15 simulator before break phys
2019-10-15 simulator phys
2019-10-16 model 1/5
2019-10-21 PR Odometry OK
2019-10-22 PR carto & local
2019-10-22 PR curv profil failure
2019-10-23 PR before noise IMU
2019-10-23 Simulation de trajectoire RL
2019-10-25 PR plot radius correction
2019-10-25 PR fix odometry
2019-10-25 PR failure after refactoring
2019-10-25 PR drift with angle correction
2019-10-26 PR mise à jour correcte de l'algo
2019-10-26 PR with noise and bias but failure at 5th turn
2019-10-26 PR plot error
2019-10-26 PR with bias failure
2019-10-27 PR without bias
2019-10-27 Modification du format de fichier circuit
2019-10-28 PR with EKFSLAM but angle pb
2019-10-28 Update of circuit drawing
    Road and center line color updated
    Trajectory removed from circuit class to allow multiple trajectories displayed.
    New Trajectory class
2019-10-28 Circuit description using float
    Circuit description can use float values for lengths.
    UnitLength value is in meters.
    Image is shown using 100px per meters by default. Parameter zoom_factor can modify ppm.
2019-10-28 PR EKF SLAM
2019-10-29 PR rem
2019-10-29 Create RL-circuit-v0.08.py
    Correction de bugs
    Ajout d'une fonction de détection de passage de ligne d'arrivée
2019-10-29 SaveImage test
2019-10-30 Engine
2019-11-02 telem lidar
2019-11-03 buggy
2019-11-06 lidar
2019-11-07 clustering
2019-11-07 cluster
2019-11-07 pres
2019-11-08 cloud
2019-11-09 gyro
2019-11-09 stm32 ok with gyro
2019-11-11 Tentative de RL
2019-11-15 proxy
2019-11-21 Updated RL framework
2019-11-22 matgps
2019-11-23 Trajectoire optimale
    Mise à jour pour permettre le multiprocessing.
    Modification de l'agent pour trouver la trajectoire optimale, et pas uniquement arriver au bout.
    Corrections de bugs
2019-12-11 Datset Tricolore
2019-12-12 training
2020-01-22 Create RM-cinématique pattes.docx
    Description de la cinématique des pattes
2020-01-23 Update RM-cinématique pattes.docx
    Ajout de la cinématique pour le multipatte chien
2020-01-23 ardurover
2020-01-25 track simple
2020-01-25 Ajout soft STM et schémas carte
2020-01-25 Trajectoire pied
2020-01-26 Cinématique inverse
2020-01-26 cinématique chien
2020-01-26 chien
2020-01-26 Soft STM32 v3
2020-02-07 tetra
2020-02-07 ciseau
2020-02-07 Scheme of 5-bar Linkage for the Inverse Geometry
2020-02-24 simulateur
2020-02-24 simu
2020-02-25 xray
2020-02-27 simuTRR
2020-02-27 meca
2020-02-27 simu TRR
2020-02-27 odrive
2020-02-29 stm32 & Simu odom
2020-02-29 occupancy map
2020-02-29 slam
2020-02-29 odrv
2020-03-02 entretoise
2020-03-04 slam debug
2020-05-20 name
2020-05-21 Update RM-cinématique pattes.docx
    MAJ doc cinématique pattes
2020-05-23 walk gait processing
2020-05-23 COCM
2020-06-10 Update STM32 SW
